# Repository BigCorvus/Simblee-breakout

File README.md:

# Simblee-breakout
breakout for the rfd77101 module

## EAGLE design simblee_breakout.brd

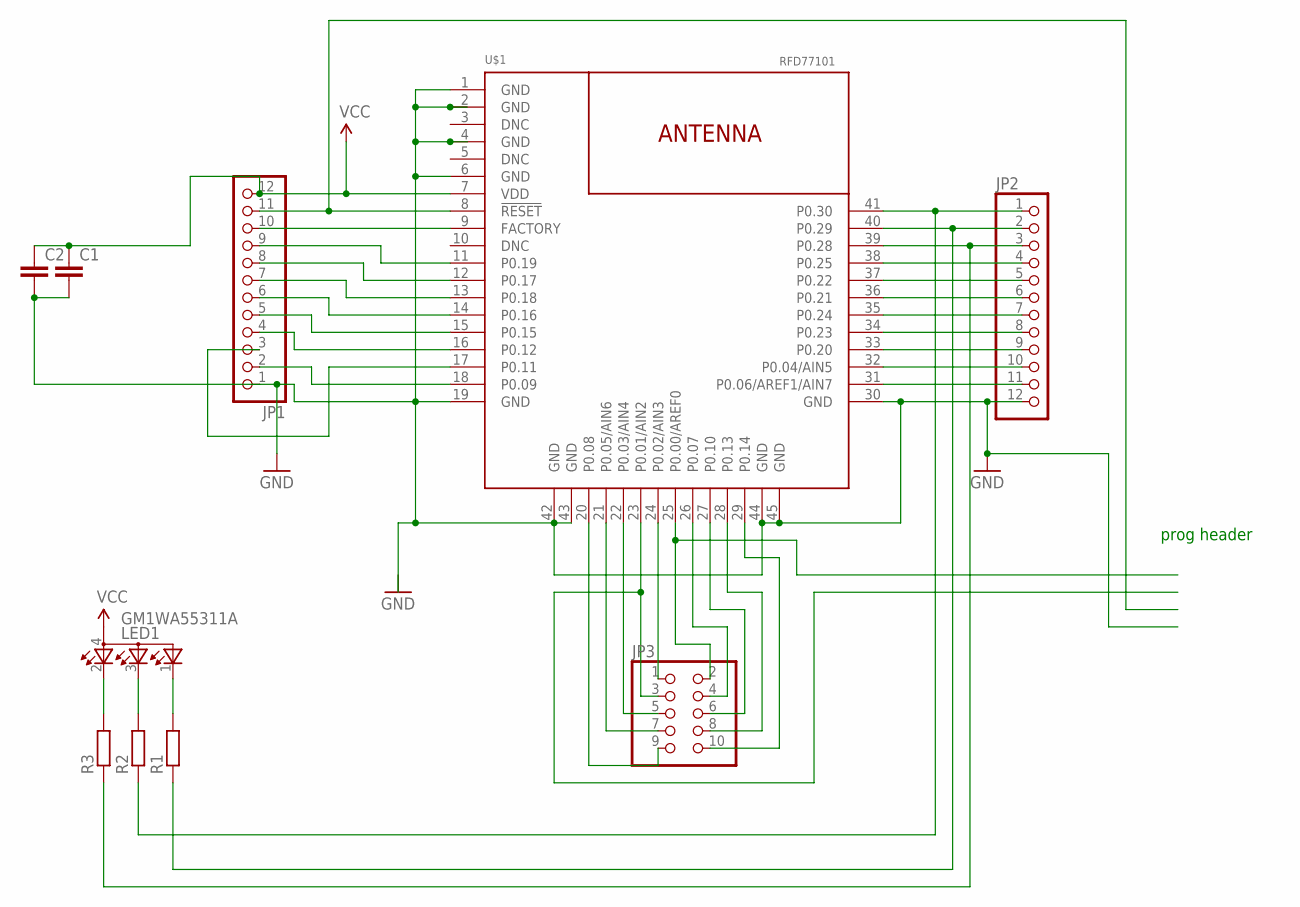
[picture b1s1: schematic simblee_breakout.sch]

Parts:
C1, C2: C-EUC0603; C0603
JP1, JP2: PINHD-1X12; 1X12
JP3: PINHD-2X5; 2X05
LED1: GM1WA55311A
R1, R2, R3: R-EU_R0603; R0603
U$1: RFD77101

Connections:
GND: C1.2, C2.2, JP1.1, JP2.12, U$1.1 (GND), U$1.2 (GND), U$1.4 (GND), U$1.6 (GND), U$1.19 (GND), U$1.30 (GND), U$1.42 (GND), U$1.43 (GND), U$1.44 (GND), U$1.45 (GND)
unnamed: JP2.7, U$1.35 (P0.24)
unnamed: LED1.2 (CRED), R3.2
unnamed: JP2.11, U$1.31 (P0.06/AREF1/AIN7)
unnamed: JP1.11, U$1.8 (!RESET!)
unnamed: JP1.10, U$1.9 (FACTORY)
unnamed: JP1.9, U$1.11 (P0.19)
unnamed: JP1.8, U$1.12 (P0.17)
unnamed: JP1.7, U$1.13 (P0.18)
unnamed: JP1.6, U$1.14 (P0.16)
unnamed: JP1.5, U$1.15 (P0.15)
unnamed: JP1.4, U$1.16 (P0.12)
unnamed: JP1.3, U$1.17 (P0.11)
unnamed: JP1.2, U$1.18 (P0.09)
unnamed: LED1.3 (CBLUE), R2.2
unnamed: JP2.2, R1.1, U$1.40 (P0.29)
unnamed: JP2.4, U$1.38 (P0.25)
unnamed: JP2.5, U$1.37 (P0.22)
unnamed: JP2.6, U$1.36 (P0.21)
unnamed: LED1.1 (CGREEN), R1.2
unnamed: JP2.8, U$1.34 (P0.23)
unnamed: JP2.9, U$1.33 (P0.20)
unnamed: JP3.1, U$1.24 (P0.02/AIN3)
unnamed: JP2.10, U$1.32 (P0.04/AIN5)
unnamed: JP3.9, U$1.20 (P0.08)
unnamed: JP3.7, U$1.21 (P0.05/AIN6)
unnamed: JP2.1, R2.1, U$1.41 (P0.30)
unnamed: JP3.3, U$1.23 (P0.01/AIN2)
unnamed: JP2.3, R3.1, U$1.39 (P0.28)
unnamed: JP3.2, U$1.25 (P0.00/AREF0)
unnamed: JP3.4, U$1.26 (P0.07)
unnamed: JP3.6, U$1.27 (P0.10)
unnamed: JP3.8, U$1.28 (P0.13)
unnamed: JP3.10, U$1.29 (P0.14)
unnamed: JP3.5, U$1.22 (P0.03/AIN4)
VCC: C1.1, C2.1, JP1.12, LED1.4 (A), U$1.7 (VDD)

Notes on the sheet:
prog header

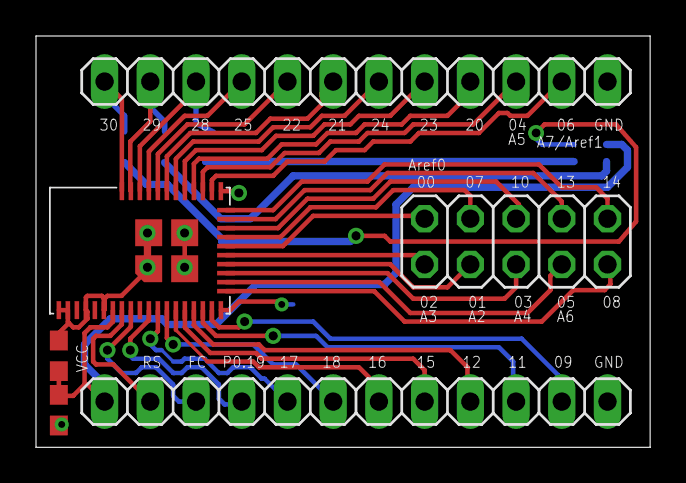
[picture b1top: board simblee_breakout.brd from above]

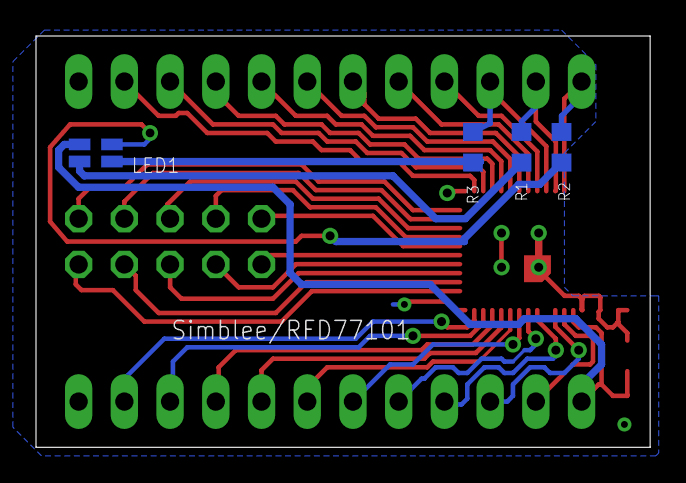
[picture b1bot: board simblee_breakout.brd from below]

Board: 2 copper layers, 34.1 x 22.9 mm, 10 parts (4 on the bottom side), 36 nets.

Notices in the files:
parts and their libraries:
RFDigital: © 2015 RF Digital Corporation
SparkFun-Aesthetics: Licensing: Creative Commons ShareAlike 4.0 International - https://creativecommons.org/licenses/by-sa/4.0
